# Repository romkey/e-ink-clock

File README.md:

# e-ink wifi clock

_This is a work in progress. I'm still testing and updating the hardware, and the software is incomplete. Build at your own risk._

Use a Waveshare epaper (e-ink) display as a digital wifi clock. The clock synchronizes its time with NTP and can show local weather using OpenWeatherMap.

The clock also supports an optional environmental sensor module, which allows it to report the temperature, humidity and air pressure in the space it's in.

It also supports an optional DS3231 I2C real time clock with battery backup module. This allows it to know the time immediately upon booting, even without NTP, and to keep time more accurately than just the ESP32 is capable of.

FInally, it also supports an optional ambient light sensor. This allows the clock to power down the e-ink module in the dark (when it is unreadable), which should extend the lifespan of the module.

# Hardware

Eagle schematics and board are in the `eagle` directory. 

_The hardware is still in testing; I cannot make any promises about its suitability for any use or its reliability._

Prices are obviously from the time I made this list. Links to parts are meant to show parts that have identical pinouts to the ones I used in the PC board layout. The specific items may become unavailable over time or the listings might even change to other parts with incompatible pinouts, so *please be careful to make sure you get parts with the correct pinouts* if you want to use the PC board - this is meant to be a guide to the parts and not a specific shopping list. 

| Part                               | AliExpress | Amazon | Notes |
|-------------------|--------:|-------:|--|
|Waveshare 4.2" epaper module | [$28.79](https://www.aliexpress.com/item/400x300-4-2inch-E-Ink-display-module-No-backlight-Ultra-low-power-consumption-SPI-interface-Compatible/32826601765.html) | [$38.99](https://www.amazon.com/gp/product/B074NR1SW2) | |
|Wemos LOLIN32 ESP32 | [$5.50](https://www.aliexpress.com/item/ESP-32-ESP32-ESP-WROOM-32-for-WeMos-D1-LOLIN32-V1-0-02-WIFI-Bluetooth-Development/32887251214.html) | [$9.99 + $4.99](https://www.amazon.com/Beaster-LOLIN32-V1-0-0-Bluetooth-Development/dp/B07KFF1GJK) | |
|BME280 breakout | [$2.50](https://www.aliexpress.com/item/High-Accuracy-3In1-BME280-Digital-Sensor-Temperature-Humidity-Barometric-Pressure-Sensor-Module-GY-BME280-I2C-SPI/32817230797.html) | [$11.20](https://www.amazon.com/gp/product/B0775XFW69) | *optional*  lets you read the temperature, hunmidity and pressure where the clock is |
|DS3231 RTC breakout | [$1.04](https://www.aliexpress.com/item/DS3231-AT24C32-IIC-High-Precision-RTC-Module-Clock-Timer-Memory-Module/2037934408.html) | [$6.99](https://www.amazon.com/gp/product/B01IXXACD0) | *optional* keeps more accurate time, works without NTP or wifi |
|photoresistor |  |  | *optional* lets the clock power off display in the dark |
|         |$37.83 | $72.16 |

Obviously AliExpress is an economical choice if you can wait a month or more for your parts to arrive. 

The printed circuit board uses breakout boards and is easy to assemble. The current version is at https://oshpark.com/shared_projects/apAIFWjg

# Software

The e-ink clock software is built using the Arduino SDK. It builds under [PlatformIO](https://platformio.org/) but with a little rearranging you could also build it with the Arduino IDE.

The application uses the [GxEPD](https://github.com/ZinggJM/GxEPD) library to drive the Waveshare display. GxEPD is a subclass of [Adafruit_GFX](https://github.com/adafruit/Adafruit-GFX-Library), so you can use its API to talk to the display. It also supports fast partial update on some Waveshare displays, which lets you write to the display much faster than a full screen write, without distracting flashing.

## Resources:

- turn an image file into a C language bitmap - [image2cpp](https://javl.github.io/image2cpp/)
- use `fontconvert` from Adafruit GFX Library to convert fonts to Adafruit GFX format

## Configuration

Copy `src/config.h-example` to `src/config.h` and set the constants in the file as you need them:
- `WIFI_SSID1`, `WIFI_PASSWORD1` - your primary WiFi SSID and password 
- `WIFI_SSID2`, `WIFI_PASSWORD2` - your backup WiFi SSID and password  - set to the same as primary if you don't have a backup
- `WIFI_SSID3`, `WIFI_PASSWORD3` - your bakup backup WiFi SSID and password  - set to the same as backup if you don't have a backup backup

## License

Permission to use this software is granted under the [MIT License](https://romkey.mit-license.org).

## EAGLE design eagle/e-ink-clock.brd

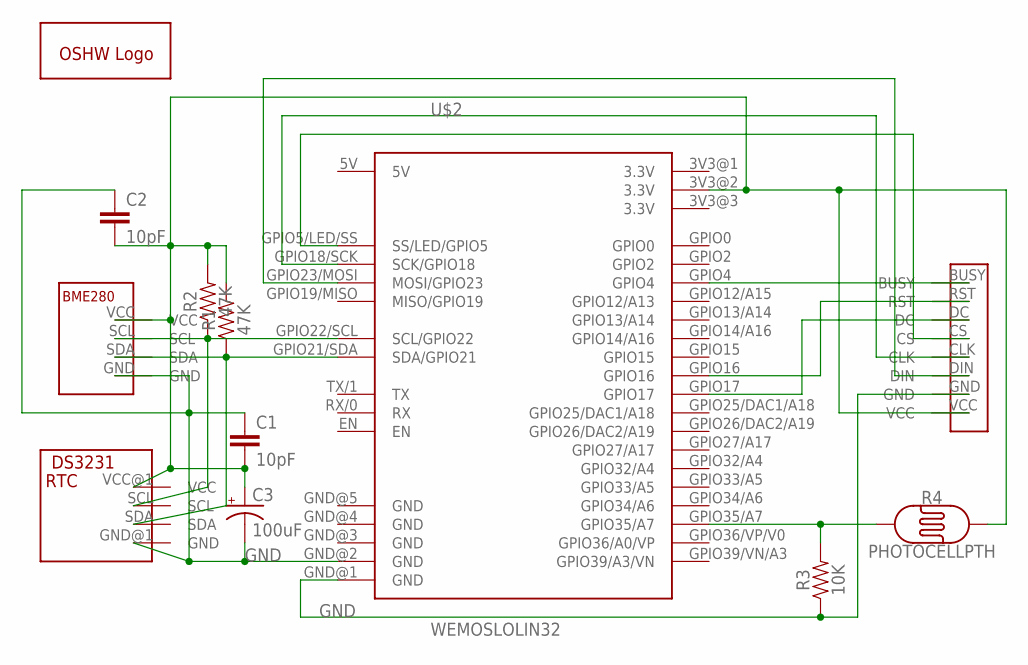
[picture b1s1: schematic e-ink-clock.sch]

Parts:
C1, C2: 10pF; CAP-PTH-SMALL2
C3: 100uF; CPOL-RADIAL-2.5MM-6.5MM
GOLD_ORB_SM1: OSHWLOGOLOGO16MM; OSHW_16MM
R1, R2: 47K; AXIAL-0.3
R3: 10K; AXIAL-0.3
R4: PHOTOCELLPTH; PHOTOCELL
U$1: WAVESHAREE-INK; WAVESHARE-EINK
U$2: WEMOSLOLIN32; LOLIN32VAR1
U$3: BME280BREAKOUTBME280; HDRV4W64P254_1X4_1016X508X838B
U$4: DS3231BREAKOUT

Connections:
3.3V: C1.2, C2.2, C3.1 (+), R1.P$2 (2), R2.P$2 (2), R4.2, U$1.VCC, U$2.3V3@2 (3.3V), U$2.3V3@3 (3.3V), U$3.VCC, U$4.VCC@1 (VCC)
5V: U$2.5V
GND: C1.1, C2.1, C3.2 (-), R3.P$1 (1), U$1.GND, U$2.GND@1 (GND), U$2.GND@2 (GND), U$3.GND, U$4.GND@1 (GND)
unnamed: U$1.CLK, U$2.GPIO18/SCK (SCK/GPIO18)
unnamed: U$1.CS, U$2.GPIO5/LED/SS (SS/LED/GPIO5)
unnamed: R2.P$1 (1), U$2.GPIO22/SCL (SCL/GPIO22), U$3.SCL, U$4.SCL
unnamed: R1.P$1 (1), U$2.GPIO21/SDA (SDA/GPIO21), U$3.SDA, U$4.SDA
unnamed: U$1.BUSY, U$2.GPIO4
unnamed: U$1.RST, U$2.GPIO16
unnamed: U$1.DC, U$2.GPIO17
unnamed: U$1.DIN, U$2.GPIO23/MOSI (MOSI/GPIO23)
unnamed: R3.P$2 (2), R4.1, U$2.GPIO35/A7

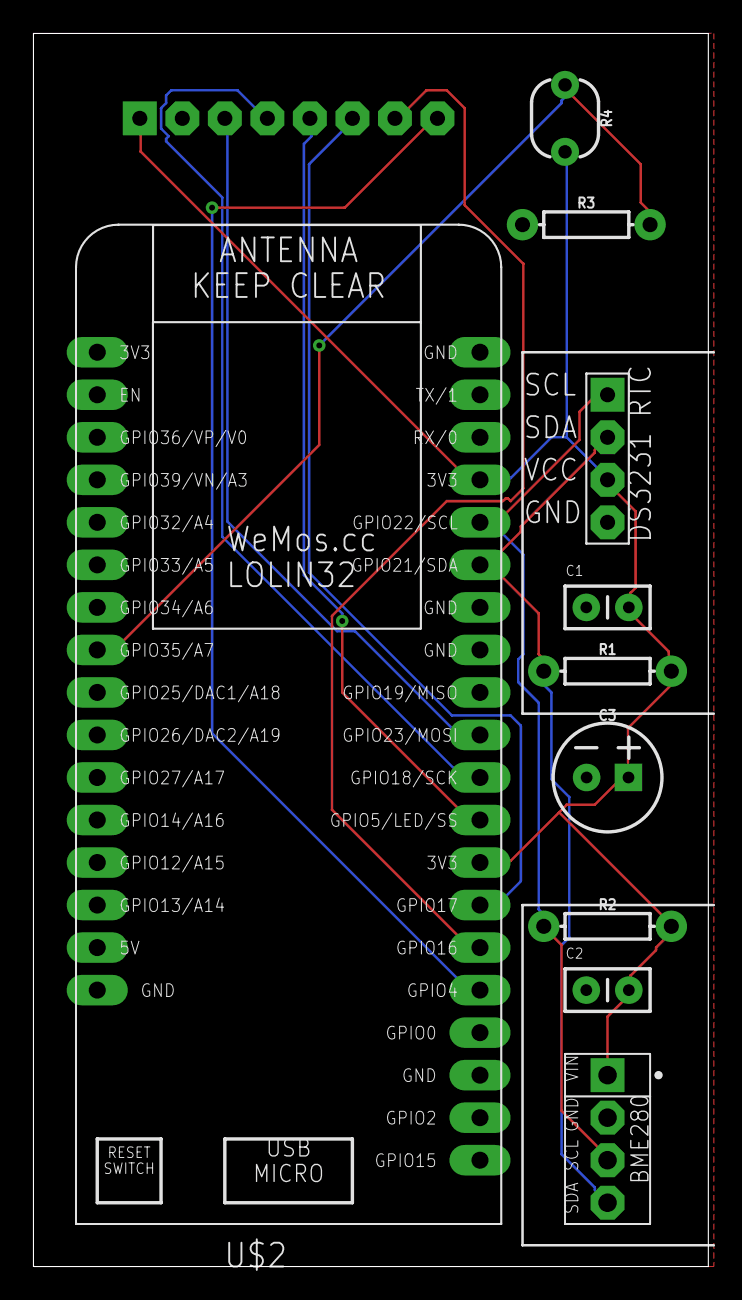
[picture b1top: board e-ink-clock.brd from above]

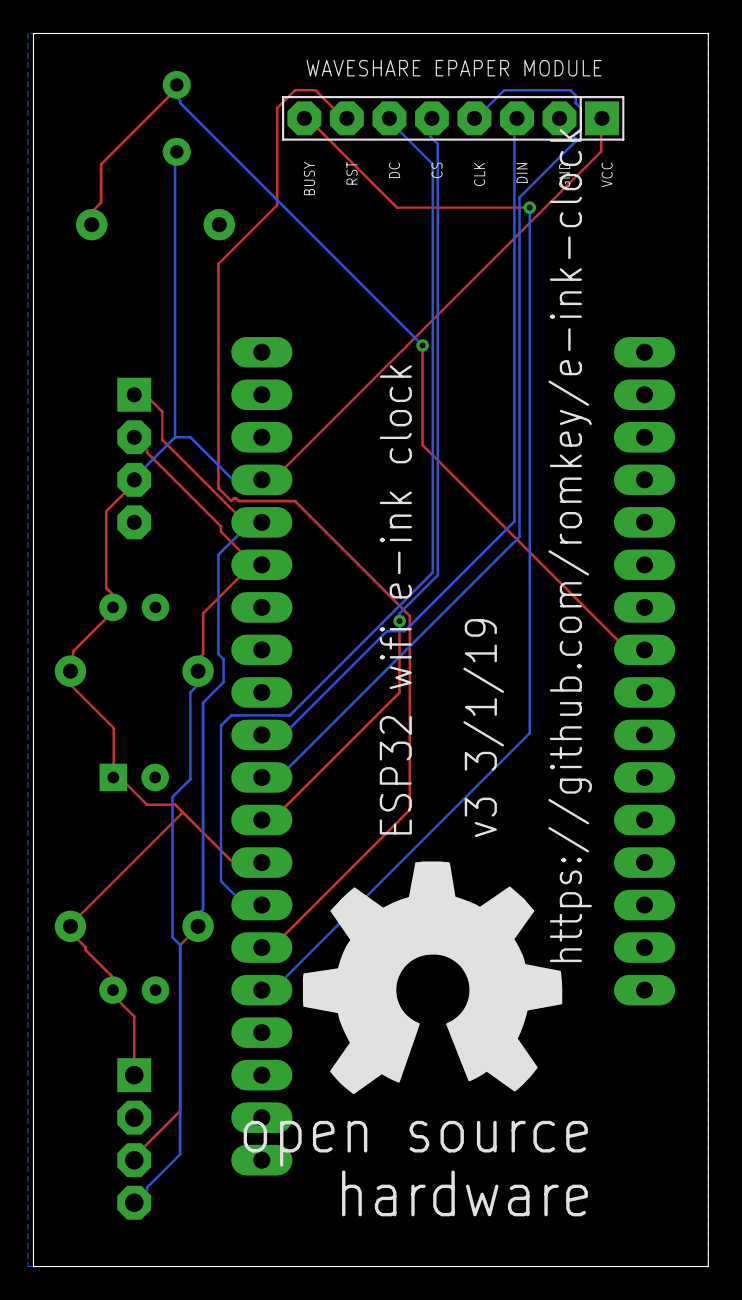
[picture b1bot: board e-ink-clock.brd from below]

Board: 2 copper layers, 40.3 x 73.7 mm, 12 parts (2 on the bottom side), 11 nets.

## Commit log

2019-02-10 initial README
2019-02-10 missing files
2019-02-19 work on UI
    example config.h file
2019-02-19 updated README with Amazon links
2019-02-19 more README updates
2019-02-22 doc changes
2019-03-02 read temperature and hunidity from a BME280 and show on display
2019-03-02 documentation updates
2019-03-02 doc update
    Eagle files
2019-05-08 a little bit of OpenWeatherMap API support
    post data to MQTT server
    font work
    track uptime
2019-06-05 add build info
    log boot on startup
    accept rehab, clock and restart commands
2019-09-18 added ping command
    platformio 4
2022-07-05 removed IFTTTWebHook use
    qualified libraries in platformio.ini
    updated example config.h file
2022-07-05 a little work on README
    updated the copyright years
    got rid of Travis
    first attempt at Github action for a compile test
2022-07-05 added test build badge to README
2022-07-05 fixed workflow badge path
2022-07-05 one more fix

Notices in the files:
parts and their libraries:
SparkFun-Resistors: Licensing: Creative Commons ShareAlike 4.0 International - https://creativecommons.org/licenses/by-sa/4.0
